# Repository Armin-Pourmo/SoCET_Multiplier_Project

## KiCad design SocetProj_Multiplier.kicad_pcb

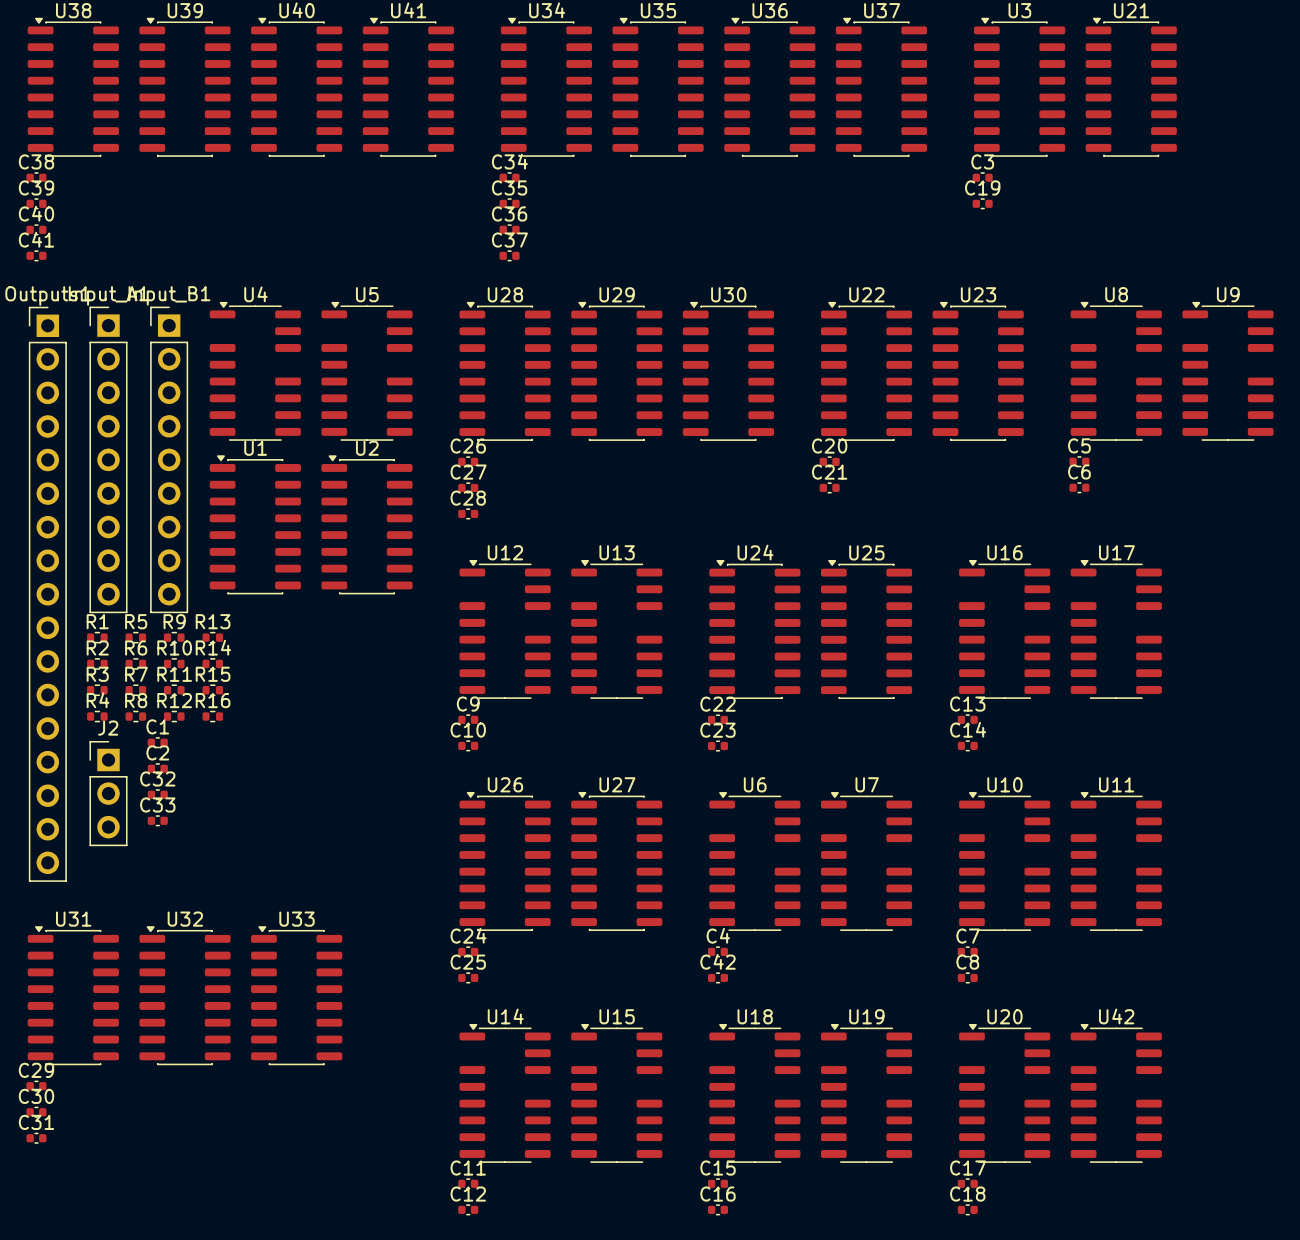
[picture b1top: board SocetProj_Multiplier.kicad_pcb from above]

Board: 2 copper layers, 104 parts (0 on the bottom side), 207 nets, no tracks yet.

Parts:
C1, C2, C32, C33: .1u; C_0402_1005Metric
C3, C19, C20, C21, C22, C23, C24, C25, C26, C27, C28, C29, C30, C31, C34, C35, C36, C37, C38, C39, C40, C41: .1uF; C_0402_1005Metric
C4, C5, C6, C7, C8, C9, C10, C11, C12, C13, C14, C15, C16, C17, C18, C42: C; C_0402_1005Metric
Input_A1: Conn_01x09_Pin; PinHeader_1x09_P2.54mm_Vertical
Input_B1: Conn_01x09_Pin; PinHeader_1x09_P2.54mm_Vertical
J2: Conn_01x03_Pin; PinHeader_1x03_P2.54mm_Vertical
Outputs1: Conn_01x17_Pin; PinHeader_1x17_P2.54mm_Vertical
R1, R2, R3, R4, R5, R6, R7, R8, R9, R10, R11, R12, R13, R14, R15, R16: 1k; R_0402_1005Metric
U1, U2, U3, U21, U22, U23, U24, U25, U26, U27, U28, U29, U30, U31, U32, U33, U34, U35, U36, U37: 74LS283; SOIC-16_3.9x9.9mm_P1.27mm
U4, U5: 74LS86; SOIC-14-16_3.9x9.9mm_P1.27mm
U6, U7, U8, U9, U10, U11, U12, U13, U14, U15, U16, U17, U18, U19, U20, U42: 74LS08; SOIC-14-16_3.9x9.9mm_P1.27mm
U38, U39, U40, U41: 74LS157; SOIC-16_3.9x9.9mm_P1.27mm

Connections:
+5V: C1.1, C2.1, C3.1, C4.2, C5.2, C6.2, C7.2, C8.2, C9.2, C10.2, C11.2, C12.2, C13.2, C14.2, C15.2, C16.2, C17.2, C18.2, C19.1, C20.1, C21.1, C22.1, C23.1, C24.1, C25.1, C26.1, C27.1, C28.1, C29.1, C30.1, C31.1, C32.1, C33.1, C34.1, C35.1, C36.1, C37.1, C38.1, C39.1, C40.1, C41.1, C42.2, U1.16 (VCC), U2.16 (VCC), U3.16 (VCC), U4.14 (VCC), U5.14 (VCC), U6.14 (VCC), U7.14 (VCC), U8.14 (VCC), U9.14 (VCC), U10.14 (VCC), U11.14 (VCC), U12.14 (VCC), U13.14 (VCC), U14.14 (VCC), U15.14 (VCC), U16.14 (VCC), U17.14 (VCC), U18.14 (VCC), U19.14 (VCC), U20.14 (VCC), U21.16 (VCC), U22.16 (VCC), U23.16 (VCC), U24.16 (VCC), U25.16 (VCC), U26.16 (VCC), U27.16 (VCC), U28.16 (VCC), U29.16 (VCC), U30.16 (VCC), U31.16 (VCC), U32.16 (VCC), U33.16 (VCC), U34.16 (VCC), U35.16 (VCC), U36.16 (VCC), U37.16 (VCC), U38.16 (VCC), U39.16 (VCC), U40.16 (VCC), U41.16 (VCC), U42.14 (VCC)
/A0: Input_A1.1, R1.1, U1.5 (A1)
/A1: Input_A1.2, R2.1, U1.3 (A2), U7.5, U9.5, U11.5, U13.5, U15.5, U17.5, U19.5, U42.5
/A2: Input_A1.3, R3.1, U1.14 (A3), U7.10, U9.10, U11.10, U13.10, U15.10, U17.10, U19.10, U42.10
/A3: Input_A1.4, R4.1, U1.12 (A4)
/A4: Input_A1.5, R5.1, U2.5 (A1)
/A5: Input_A1.6, R6.1, U2.3 (A2), U6.5, U8.5, U10.5, U12.5, U14.5, U16.5, U18.5, U20.5
/A6: Input_A1.7, R7.1, U2.14 (A3), U6.10, U8.10, U10.10, U12.10, U14.10, U16.10, U18.10, U20.10
/A7: Input_A1.8, R8.1, U2.12 (A4)
/Add0: U1.4 (S1), U38.3 (I1a)
/Add1: U1.1 (S2), U38.6 (I1b)
/Add2: U1.13 (S3), U38.10 (I1c)
/Add3: U1.10 (S4), U38.13 (I1d)
/Add4: U2.4 (S1), U39.3 (I1a)
/Add5: U2.1 (S2), U39.6 (I1b)
/Add6: U2.13 (S3), U39.10 (I1c)
/Add7: U2.10 (S4), U39.13 (I1d)
/Add8: U2.9 (C4), U40.3 (I1a)
/B0: Input_B1.1, R9.1, U6.1, U6.4, U6.9, U6.12, U7.1, U7.4, U7.9, U7.12
/B1: Input_B1.2, R10.1, U4.5, U8.1, U8.4, U8.9, U8.12, U9.1, U9.4, U9.9, U9.12
/B2: Input_B1.3, R11.1, U4.10, U10.1, U10.4, U10.9, U10.12, U11.1, U11.4, U11.9, U11.12
/B3: Input_B1.4, R12.1, U12.1, U12.4, U12.9, U12.12, U13.1, U13.4, U13.9, U13.12
/B4: Input_B1.5, R13.1, U14.1, U14.4, U14.9, U14.12, U15.1, U15.4, U15.9, U15.12
/B5: Input_B1.6, R14.1, U5.5, U16.1, U16.4, U16.9, U16.12, U17.1, U17.4, U17.9, U17.12
/B6: Input_B1.7, R15.1, U5.10, U18.1, U18.4, U18.9, U18.12, U19.1, U19.4, U19.9, U19.12
/B7: Input_B1.8, R16.1, U20.1, U20.4, U20.9, U20.12, U42.1, U42.4, U42.9, U42.12
/C0: J2.1, U1.7 (C0), U4.1, U4.4, U4.9, U4.12, U5.1, U5.4, U5.9, U5.12
/C1: J2.2, U38.1 (S), U39.1 (S), U40.1 (S), U41.1 (S)
/C_Out_1: U1.9 (C4), U2.7 (C0)
/Dadda_Multiplier/B00: U7.3, U28.5 (A1)
/Dadda_Multiplier/B01: U3.4 (S1), U28.3 (A2)
/Dadda_Multiplier/B02: U3.1 (S2), U28.14 (A3)
/Dadda_Multiplier/B03: U3.13 (S3), U28.12 (A4)
/Dadda_Multiplier/B04: U3.10 (S4), U29.5 (A1)
/Dadda_Multiplier/B05: U21.4 (S1), U29.3 (A2)
/Dadda_Multiplier/B06: U21.1 (S2), U29.14 (A3)
/Dadda_Multiplier/B07: U21.13 (S3), U29.12 (A4)
/Dadda_Multiplier/B08: U21.10 (S4), U30.5 (A1)
/Dadda_Multiplier/B09: U21.9 (C4), U30.3 (A2)
/Dadda_Multiplier/B10: U11.3, U28.15 (B3)
/Dadda_Multiplier/B11: U22.4 (S1), U28.11 (B4)
/Dadda_Multiplier/B12: U22.1 (S2), U29.6 (B1)
/Dadda_Multiplier/B13: U22.13 (S3), U29.2 (B2)
/Dadda_Multiplier/B14: U22.10 (S4), U29.15 (B3)
/Dadda_Multiplier/B15: U23.4 (S1), U29.11 (B4)
/Dadda_Multiplier/B16: U23.1 (S2), U30.6 (B1)
/Dadda_Multiplier/B17: U23.13 (S3), U30.2 (B2)
/Dadda_Multiplier/B18: U23.10 (S4), U30.15 (B3)
/Dadda_Multiplier/B19: U23.9 (C4), U30.11 (B4)
/Dadda_Multiplier/B20: U15.3, U31.5 (A1)
/Dadda_Multiplier/B21: U24.4 (S1), U31.3 (A2)
/Dadda_Multiplier/B22: U24.1 (S2), U31.14 (A3)
/Dadda_Multiplier/B23: U24.13 (S3), U31.12 (A4)
/Dadda_Multiplier/B24: U24.10 (S4), U32.5 (A1)
/Dadda_Multiplier/B25: U25.4 (S1), U32.3 (A2)
/Dadda_Multiplier/B26: U25.1 (S2), U32.14 (A3)
/Dadda_Multiplier/B27: U25.13 (S3), U32.12 (A4)
/Dadda_Multiplier/B28: U25.10 (S4), U33.5 (A1)
/Dadda_Multiplier/B29: U25.9 (C4), U33.3 (A2)
/Dadda_Multiplier/B30: U19.3, U31.15 (B3)
/Dadda_Multiplier/B31: U26.4 (S1), U31.11 (B4)
/Dadda_Multiplier/B32: U26.1 (S2), U32.6 (B1)
/Dadda_Multiplier/B33: U26.13 (S3), U32.2 (B2)
/Dadda_Multiplier/B34: U26.10 (S4), U32.15 (B3)
/Dadda_Multiplier/B35: U27.4 (S1), U32.11 (B4)
/Dadda_Multiplier/B36: U27.1 (S2), U33.6 (B1)
/Dadda_Multiplier/B37: U27.13 (S3), U33.2 (B2)
/Dadda_Multiplier/B38: U27.10 (S4), U33.15 (B3)
/Dadda_Multiplier/B39: U27.9 (C4), U33.11 (B4)
/Dadda_Multiplier/D00: U28.4 (S1), U34.5 (A1)
/Dadda_Multiplier/D01: U28.1 (S2), U34.3 (A2)
/Dadda_Multiplier/D02: U28.13 (S3), U34.14 (A3)
/Dadda_Multiplier/D03: U28.10 (S4), U34.12 (A4)
/Dadda_Multiplier/D04: U29.4 (S1), U35.5 (A1)
/Dadda_Multiplier/D05: U29.1 (S2), U35.3 (A2)
/Dadda_Multiplier/D06: U29.13 (S3), U35.14 (A3)
/Dadda_Multiplier/D07: U29.10 (S4), U35.12 (A4)
/Dadda_Multiplier/D08: U30.4 (S1), U36.5 (A1)
/Dadda_Multiplier/D09: U30.1 (S2), U36.3 (A2)
/Dadda_Multiplier/D10: U30.13 (S3), U36.14 (A3)
/Dadda_Multiplier/D11: U30.10 (S4), U36.12 (A4)
/Dadda_Multiplier/D12: U30.9 (C4), U37.5 (A1)
/Dadda_Multiplier/E00: U31.4 (S1), U35.6 (B1)
/Dadda_Multiplier/E01: U31.1 (S2), U35.2 (B2)
/Dadda_Multiplier/E02: U31.13 (S3), U35.15 (B3)
/Dadda_Multiplier/E03: U31.10 (S4), U35.11 (B4)
/Dadda_Multiplier/E04: U32.4 (S1), U36.6 (B1)
/Dadda_Multiplier/E05: U32.1 (S2), U36.2 (B2)
/Dadda_Multiplier/E06: U32.13 (S3), U36.15 (B3)
/Dadda_Multiplier/E07: U32.10 (S4), U36.11 (B4)
/Dadda_Multiplier/E08: U33.4 (S1), U37.6 (B1)
/Dadda_Multiplier/E09: U33.1 (S2), U37.2 (B2)
/Dadda_Multiplier/E10: U33.13 (S3), U37.15 (B3)
/Dadda_Multiplier/E11: U33.10 (S4), U37.11 (B4)
/Dadda_Multiplier/E12: U33.9 (C4), U37.9 (C4)
/Dadda_Multiplier/FinalTree/carry1: U34.9 (C4), U35.7 (C0)
/Dadda_Multiplier/FinalTree/carry2: U35.9 (C4), U36.7 (C0)
/Dadda_Multiplier/FinalTree/carry3: U36.9 (C4), U37.7 (C0)
/Dadda_Multiplier/P01: U3.5 (A1), U7.6
/Dadda_Multiplier/P02: U3.3 (A2), U7.8
/Dadda_Multiplier/P03: U3.14 (A3), U7.11
/Dadda_Multiplier/P04: U3.12 (A4), U6.3
/Dadda_Multiplier/P05: U6.6, U21.5 (A1)
/Dadda_Multiplier/P06: U6.8, U21.3 (A2)
/Dadda_Multiplier/P07: U6.11, U21.14 (A3)
/Dadda_Multiplier/P10: U3.6 (B1), U9.3
/Dadda_Multiplier/P11: U3.2 (B2), U9.6
/Dadda_Multiplier/P12: U3.15 (B3), U9.8
/Dadda_Multiplier/P13: U3.11 (B4), U9.11
/Dadda_Multiplier/P14: U8.3, U21.6 (B1)
/Dadda_Multiplier/P15: U8.6, U21.2 (B2)
/Dadda_Multiplier/P16: U8.8, U21.15 (B3)
/Dadda_Multiplier/P17: U8.11, U21.11 (B4)
/Dadda_Multiplier/P21: U11.6, U22.5 (A1)
/Dadda_Multiplier/P22: U11.8, U22.3 (A2)
/Dadda_Multiplier/P23: U11.11, U22.14 (A3)
/Dadda_Multiplier/P24: U10.3, U22.12 (A4)
/Dadda_Multiplier/P25: U10.6, U23.5 (A1)
/Dadda_Multiplier/P26: U10.8, U23.3 (A2)
/Dadda_Multiplier/P27: U10.11, U23.14 (A3)
/Dadda_Multiplier/P30: U13.3, U22.6 (B1)
/Dadda_Multiplier/P31: U13.6, U22.2 (B2)
/Dadda_Multiplier/P32: U13.8, U22.15 (B3)
/Dadda_Multiplier/P33: U13.11, U22.11 (B4)
/Dadda_Multiplier/P34: U12.3, U23.6 (B1)
/Dadda_Multiplier/P35: U12.6, U23.2 (B2)
/Dadda_Multiplier/P36: U12.8, U23.15 (B3)
/Dadda_Multiplier/P37: U12.11, U23.11 (B4)
/Dadda_Multiplier/P41: U15.6, U24.5 (A1)
/Dadda_Multiplier/P42: U15.8, U24.3 (A2)
/Dadda_Multiplier/P43: U15.11, U24.14 (A3)
/Dadda_Multiplier/P44: U14.3, U24.12 (A4)
/Dadda_Multiplier/P45: U14.6, U25.5 (A1)
/Dadda_Multiplier/P46: U14.8, U25.3 (A2)
/Dadda_Multiplier/P47: U14.11, U25.14 (A3)
/Dadda_Multiplier/P50: U17.3, U24.6 (B1)
/Dadda_Multiplier/P51: U17.6, U24.2 (B2)
/Dadda_Multiplier/P52: U17.8, U24.15 (B3)
/Dadda_Multiplier/P53: U17.11, U24.11 (B4)
/Dadda_Multiplier/P54: U16.3, U25.6 (B1)
/Dadda_Multiplier/P55: U16.6, U25.2 (B2)
/Dadda_Multiplier/P56: U16.8, U25.15 (B3)
/Dadda_Multiplier/P57: U16.11, U25.11 (B4)
/Dadda_Multiplier/P61: U19.6, U26.5 (A1)
/Dadda_Multiplier/P62: U19.8, U26.3 (A2)
/Dadda_Multiplier/P63: U19.11, U26.14 (A3)
/Dadda_Multiplier/P64: U18.3, U26.12 (A4)
/Dadda_Multiplier/P65: U18.6, U27.5 (A1)
/Dadda_Multiplier/P66: U18.8, U27.3 (A2)
/Dadda_Multiplier/P67: U18.11, U27.14 (A3)
/Dadda_Multiplier/P70: U26.6 (B1), U42.3
/Dadda_Multiplier/P71: U26.2 (B2), U42.6
/Dadda_Multiplier/P72: U26.15 (B3), U42.8
/Dadda_Multiplier/P73: U26.11 (B4), U42.11
/Dadda_Multiplier/P74: U20.3, U27.6 (B1)
/Dadda_Multiplier/P75: U20.6, U27.2 (B2)
/Dadda_Multiplier/P76: U20.8, U27.15 (B3)
/Dadda_Multiplier/P77: U20.11, U27.11 (B4)
/Dadda_Multiplier/Tree00/Carry1: U3.9 (C4), U21.7 (C0)
/Dadda_Multiplier/Tree01/Carry0: U28.9 (C4), U29.7 (C0)
/Dadda_Multiplier/Tree01/Carry1: U29.9 (C4), U30.7 (C0)
/Dadda_Multiplier/Tree1/Carry1: U22.9 (C4), U23.7 (C0)
/Dadda_Multiplier/Tree2/Carry1: U24.9 (C4), U25.7 (C0)
/Dadda_Multiplier/Tree3/Carry1: U26.9 (C4), U27.7 (C0)
/Dadda_Multiplier/Tree4/Carry0: U31.9 (C4), U32.7 (C0)
/Dadda_Multiplier/Tree4/Carry1: U32.9 (C4), U33.7 (C0)
/M0: U34.4 (S1), U38.2 (I0a)
/M1: U34.1 (S2), U38.5 (I0b)
/M2: U34.13 (S3), U38.11 (I0c)
/M3: U34.10 (S4), U38.14 (I0d)
/M4: U35.4 (S1), U39.2 (I0a)
/M5: U35.1 (S2), U39.5 (I0b)
/M6: U35.13 (S3), U39.11 (I0c)
/M7: U35.10 (S4), U39.14 (I0d)
/M8: U36.4 (S1), U40.2 (I0a)
/M9: U36.1 (S2), U40.5 (I0b)
/M10: U36.13 (S3), U40.11 (I0c)
/M11: U36.10 (S4), U40.14 (I0d)
/M12: U37.4 (S1), U41.2 (I0a)
/M13: U37.1 (S2), U41.5 (I0b)
/M14: U37.13 (S3), U41.11 (I0c)
/M15: U37.10 (S4), U41.14 (I0d)
/RA1: U1.6 (B1), U4.3
/RA2: U1.2 (B2), U4.6
/RA3: U1.15 (B3), U4.8
/RA4: U1.11 (B4), U4.11
/RB1: U2.6 (B1), U5.3
/RB2: U2.2 (B2), U5.6
/RB3: U2.15 (B3), U5.8
/RB4: U2.11 (B4), U5.11
/Z0: Outputs1.1, U38.4 (Za)
/Z1: Outputs1.2, U38.7 (Zb)
/Z2: Outputs1.3, U38.9 (Zc)
/Z3: Outputs1.4, U38.12 (Zd)
/Z4: Outputs1.5, U39.4 (Za)
/Z5: Outputs1.6, U39.7 (Zb)
/Z6: Outputs1.7, U39.9 (Zc)
/Z7: Outputs1.8, U39.12 (Zd)
/Z8: Outputs1.9, U40.4 (Za)
/Z9: Outputs1.10, U40.7 (Zb)
/Z10: Outputs1.11, U40.9 (Zc)
/Z11: Outputs1.12, U40.12 (Zd)
/Z12: Outputs1.13, U41.4 (Za)
/Z13: Outputs1.14, U41.7 (Zb)
/Z14: Outputs1.15, U41.9 (Zc)
/Z15: Outputs1.16, U41.12 (Zd)
GND: C1.2, C2.2, C3.2, C4.1, C5.1, C6.1, C7.1, C8.1, C9.1, C10.1, C11.1, C12.1, C13.1, C14.1, C15.1, C16.1, C17.1, C18.1, C19.2, C20.2, C21.2, C22.2, C23.2, C24.2, C25.2, C26.2, C27.2, C28.2, C29.2, C30.2, C31.2, C32.2, C33.2, C34.2, C35.2, C36.2, C37.2, C38.2, C39.2, C40.2, C41.2, C42.1, Input_A1.9, Input_B1.9, J2.3, Outputs1.17, R1.2, R2.2, R3.2, R4.2, R5.2, R6.2, R7.2, R8.2, R9.2, R10.2, R11.2, R12.2, R13.2, R14.2, R15.2, R16.2, U1.8 (GND), U2.8 (GND), U3.7 (C0), U3.8 (GND), U4.7 (GND), U5.7 (GND), U6.7 (GND), U7.7 (GND), U8.7 (GND), U9.7 (GND), U10.7 (GND), U11.7 (GND), U12.7 (GND), U13.7 (GND), U14.7 (GND), U15.7 (GND), U16.7 (GND), U17.7 (GND), U18.7 (GND), U19.7 (GND), U20.7 (GND), U21.8 (GND), U21.12 (A4), U22.7 (C0), U22.8 (GND), U23.8 (GND), U23.12 (A4), U24.7 (C0), U24.8 (GND), U25.8 (GND), U25.12 (A4), U26.7 (C0), U26.8 (GND), U27.8 (GND), U27.12 (A4), U28.2 (B2), U28.6 (B1), U28.7 (C0), U28.8 (GND), U29.8 (GND), U30.8 (GND), U30.12 (A4), U30.14 (A3), U31.2 (B2), U31.6 (B1), U31.7 (C0), U31.8 (GND), U32.8 (GND), U33.8 (GND), U33.12 (A4), U33.14 (A3), U34.2 (B2), U34.6 (B1), U34.7 (C0), U34.8 (GND), U34.11 (B4), U34.15 (B3), U35.8 (GND), U36.8 (GND), U37.3 (A2), U37.8 (GND), U37.12 (A4), U37.14 (A3), U38.8 (GND), U38.15 (E), U39.8 (GND), U39.15 (E), U40.6 (I1b), U40.8 (GND), U40.10 (I1c), U40.13 (I1d), U40.15 (E), U41.3 (I1a), U41.6 (I1b), U41.8 (GND), U41.10 (I1c), U41.13 (I1d), U41.15 (E), U42.7 (GND)

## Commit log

2026-03-14 second commit
2026-03-15 added schematic for 8 bit inputs and their respective pulldownresistors. Added full adders and began addition module, needs to route outputs still
2026-03-15 removed unnesccary files
2026-03-18 Added subtraction capabilities via Complement of 2 subtraction
2026-03-18 split components into seperate hierarchal modules with respective hierarchal tags. Need to figure out how to connect between modules still
2026-03-31 Begun Dadda logic
2026-04-02 Added hierarchal partial product outputs, need to complete treemultiplier
2026-04-02 test-image
2026-04-02 remove image
2026-04-02 Added first set of condensing adders, down to 4 rows total of Partials to add
2026-04-03 Finished schematic, need to look at power output of the mux potentially to drive LED pins, otherwise logic SHOULD be done
2026-04-04 Fixed ERC issues and applied Footprints
